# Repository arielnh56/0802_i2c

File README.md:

# 0802_i2c
I2C backpack shim for 0802 LCD

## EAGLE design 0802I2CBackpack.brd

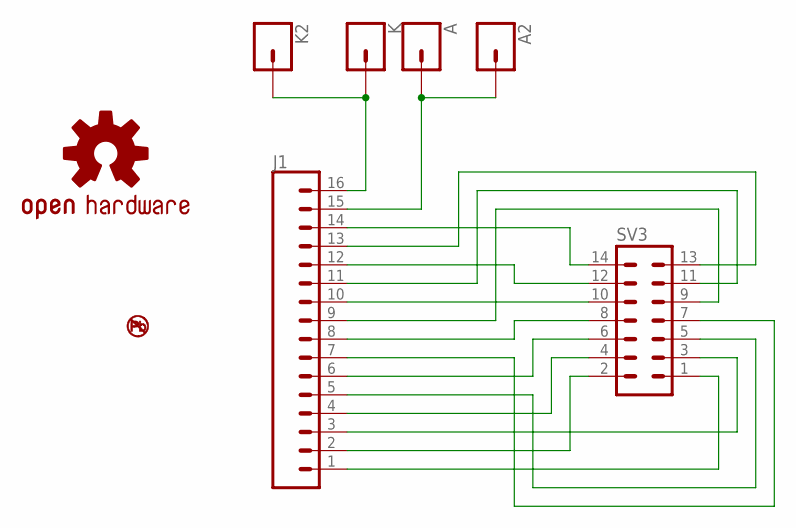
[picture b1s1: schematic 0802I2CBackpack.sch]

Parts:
A, A2: CONN_01; 1X01
J1: CONN_16; 1X16
K, K2: CONN_01; 1X01
LOGO1: OSHW-LOGOL; OSHW-LOGO-L
LOGO2: NO_PB_LOGO; NO_PB_LOGO_0.120
SV3: MA07-2

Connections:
A: A.1, A2.1, J1.15
D0: J1.7, SV3.7
D1: J1.8, SV3.8
D2: J1.9, SV3.9
D3: J1.10, SV3.10
D4: J1.11, SV3.11
D5: J1.12, SV3.12
D6: J1.13, SV3.13
D7: J1.14, SV3.14
E: J1.6, SV3.6
GND: J1.1, SV3.1
K: J1.16, K.1, K2.1
RS: J1.4, SV3.4
RW: J1.5, SV3.5
V0: J1.3, SV3.3
VDD: J1.2, SV3.2

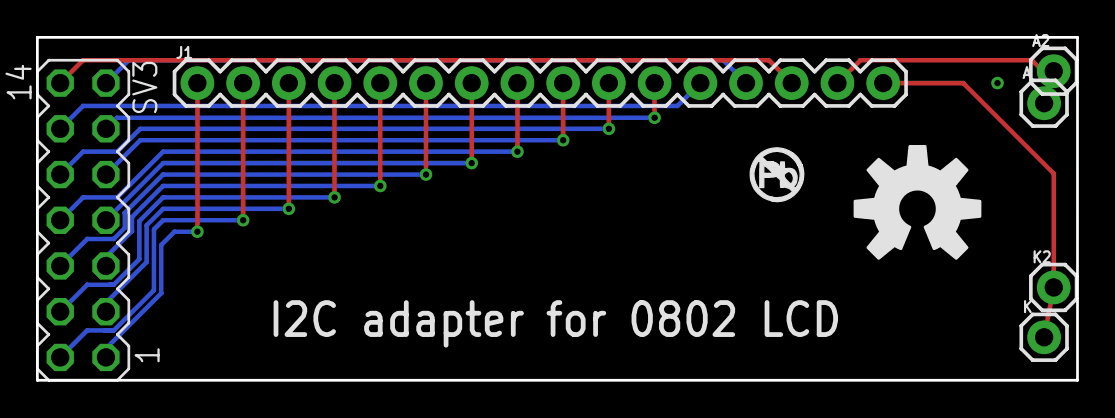
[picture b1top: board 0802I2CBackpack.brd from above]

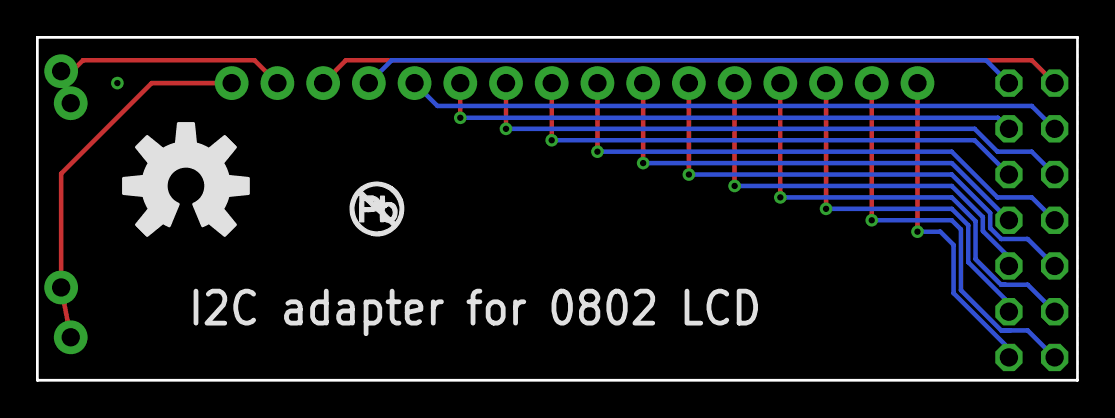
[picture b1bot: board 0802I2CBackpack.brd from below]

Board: 2 copper layers, 57.8 x 19.1 mm, 10 parts (2 on the bottom side), 16 nets.

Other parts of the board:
LOGO3: NO_PB_LOGO; NO_PB_LOGO_0.120
LOGO4: OSHW-LOGOL; OSHW-LOGO-L

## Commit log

2017-10-03 Added eagle design files

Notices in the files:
parts and their libraries:
SparkFun-Connectors: Licensing: Creative Commons ShareAlike 4.0 International - https://creativecommons.org/licenses/by-sa/4.0
